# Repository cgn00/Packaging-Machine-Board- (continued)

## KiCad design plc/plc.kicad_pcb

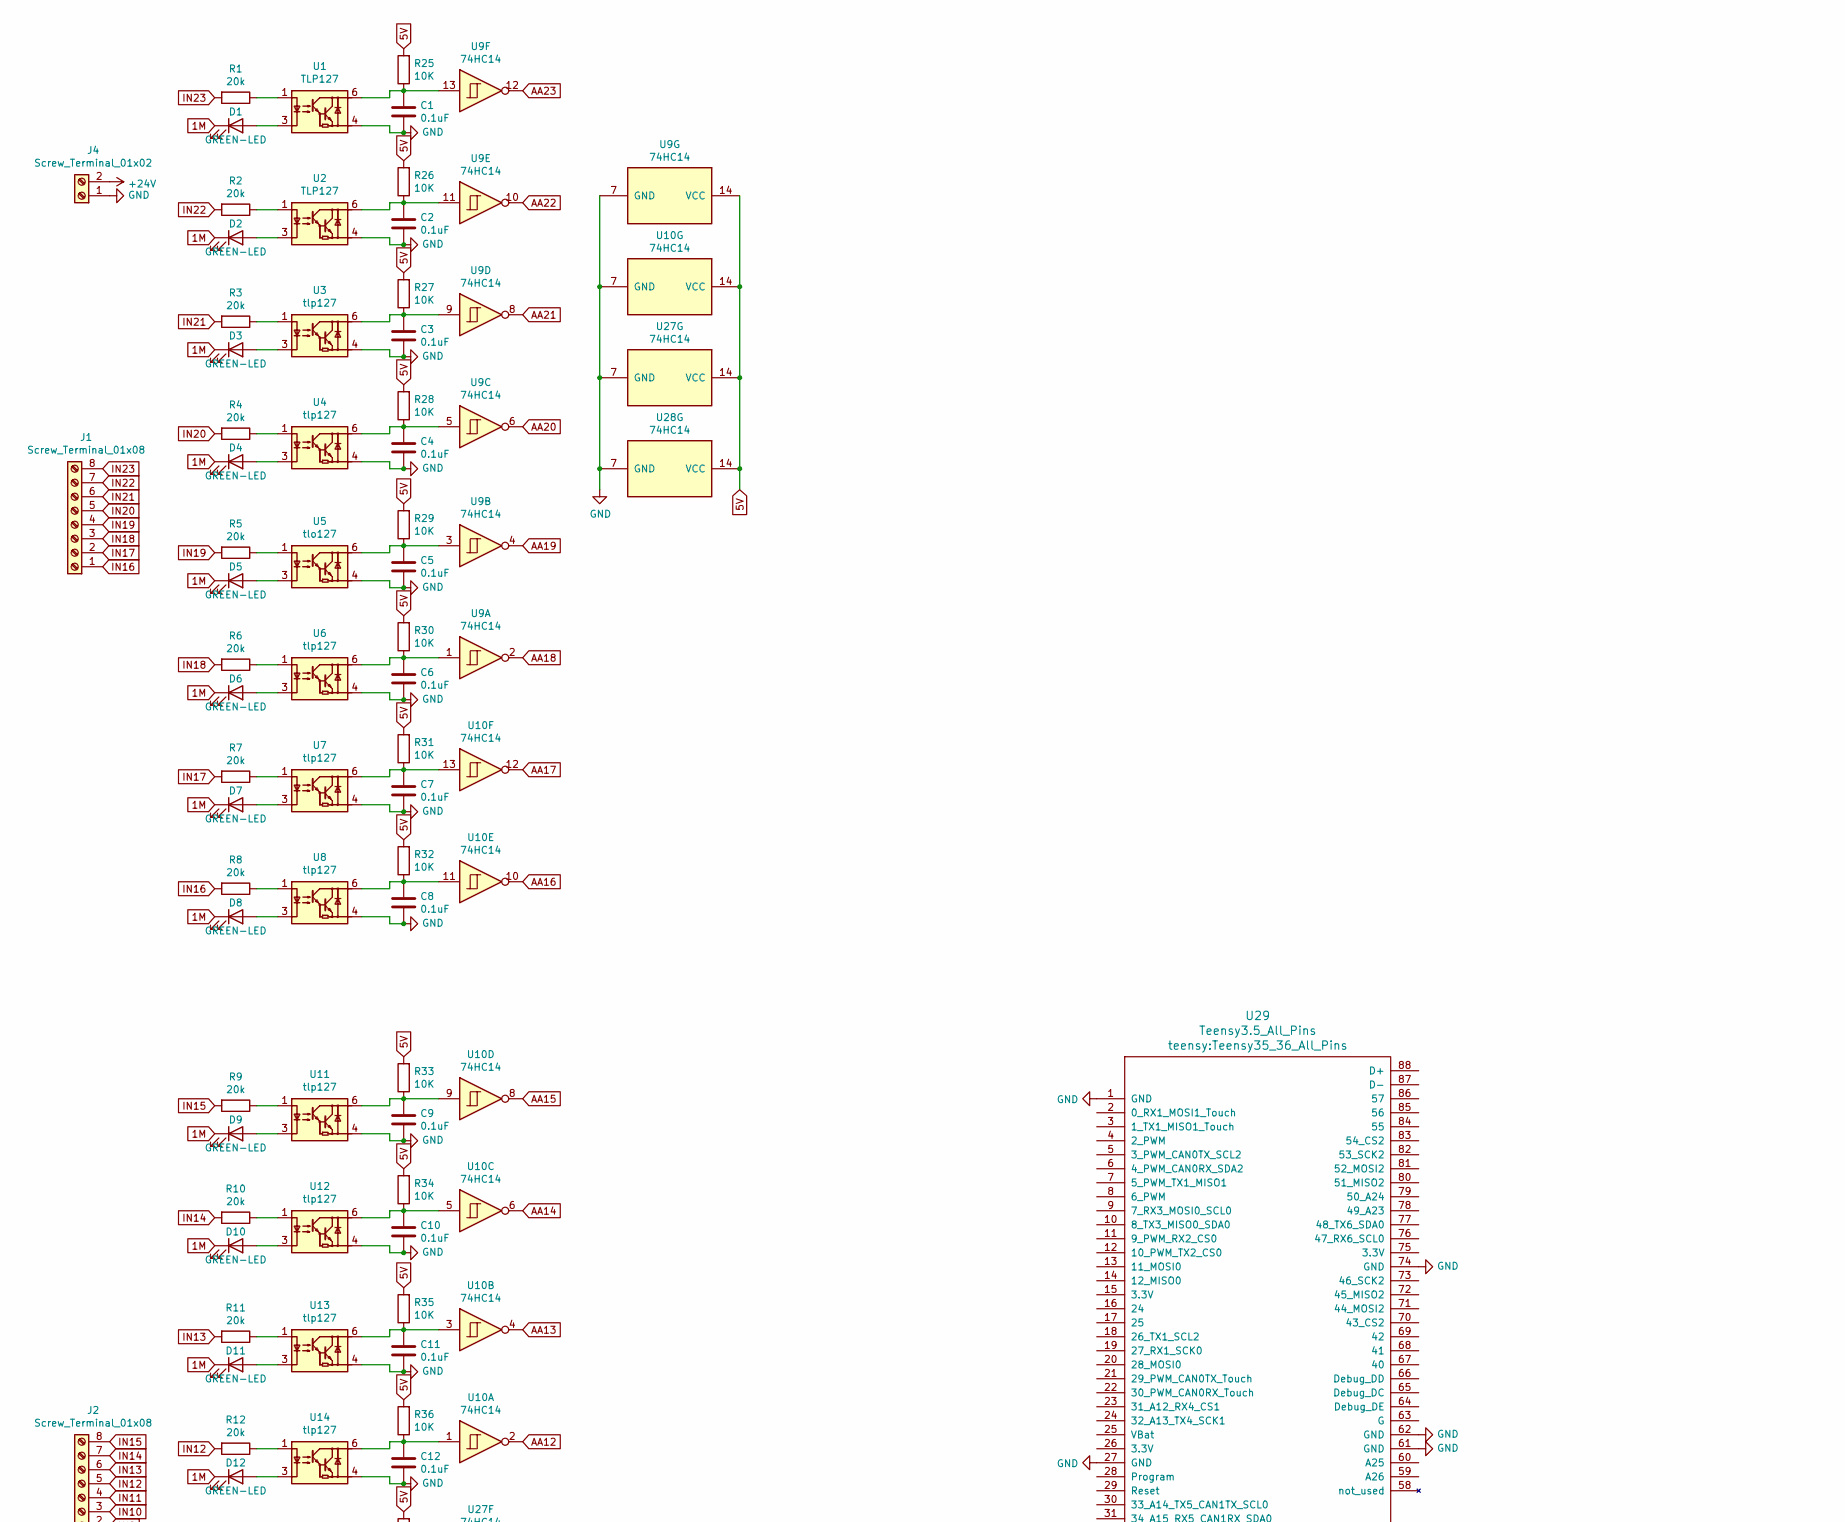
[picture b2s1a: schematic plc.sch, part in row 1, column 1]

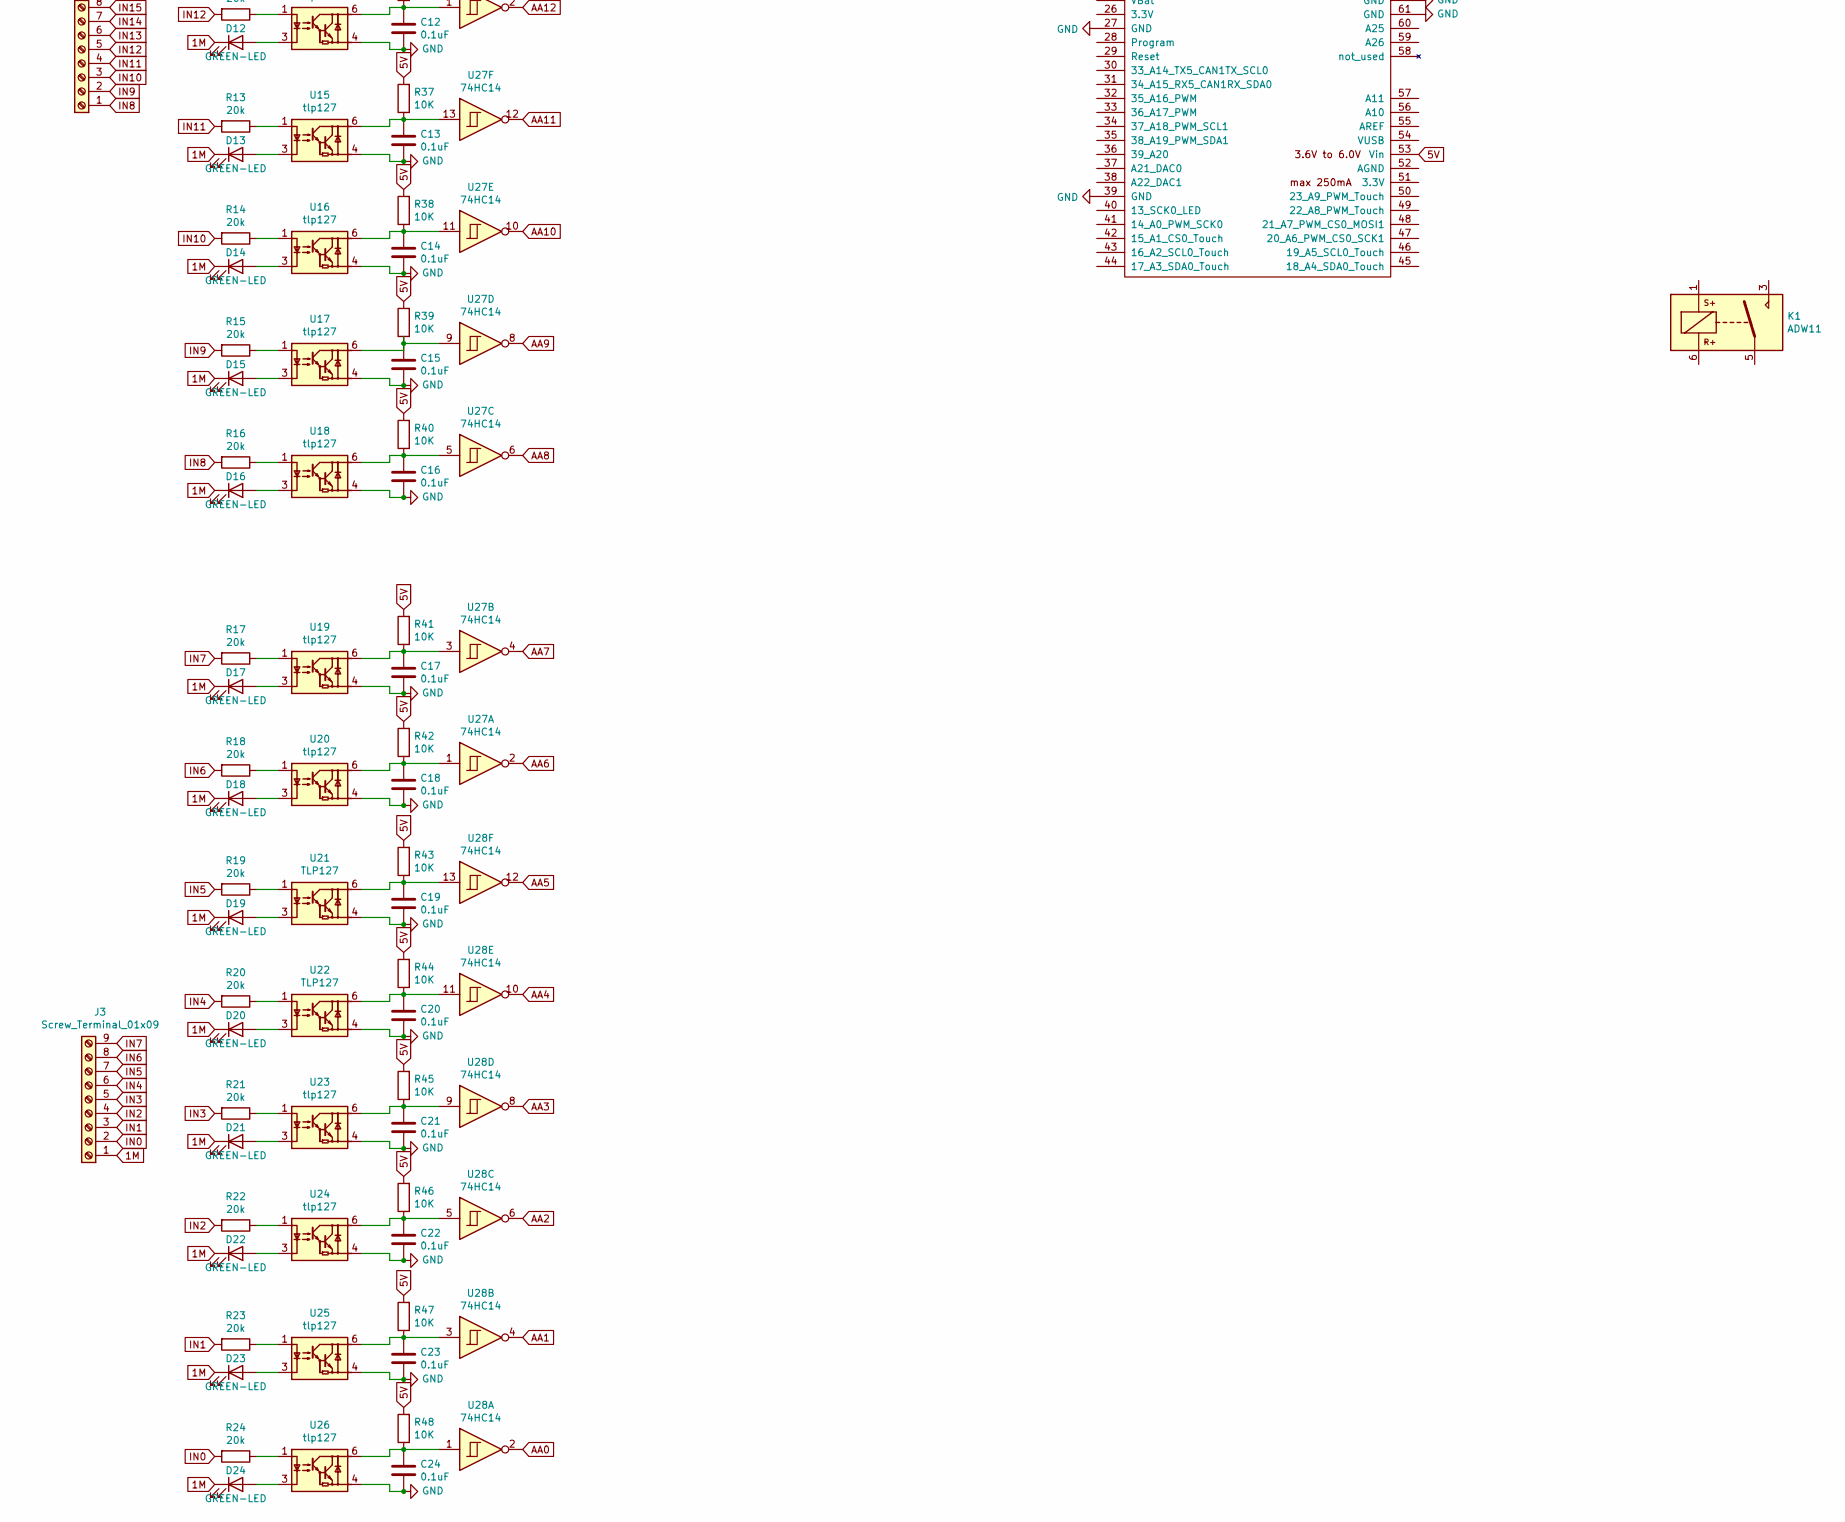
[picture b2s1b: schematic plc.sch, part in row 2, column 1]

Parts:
C1, C2, C3, C4, C5, C6, C7, C8, C9, C10, C11, C12, C13, C14, C15, C16, C17, C18, C19, C20, C21, C22, C23, C24: 0.1uF; C_1206_3216Metric
D1, D2, D3, D4, D5, D6, D7, D8, D9, D10, D11, D12, D13, D14, D15, D16, D17, D18, D19, D20, D21, D22, D23, D24: GREEN-LED; LED_1206_3216Metric_Castellated
J1, J2: Screw_Terminal_01x08; Altech_AK300_1x08_P5.00mm_45-Degree
J3: Screw_Terminal_01x09; Altech_AK300_1x09_P5.00mm_45-Degree
J4: Screw_Terminal_01x02; Altech_AK300_1x02_P5.00mm_45-Degree
K1: ADW11; Relay_1P1T_NO_10x24x18.8mm_Panasonic_ADW11xxxxW_THT
R1, R2, R3, R4, R5, R6, R7, R8, R9, R10, R11, R12, R13, R14, R15, R16, R17, R18, R19, R20, R21, R22, R23, R24: 20k; R_1206_3216Metric_Pad1.30x1.75mm_HandSolder
R25, R26, R27, R28, R29, R30, R31, R32, R33, R34, R35, R36, R37, R38, R39, R40, R41, R42, R43, R44, R45, R46, R47, R48: 10K; R_0603_1608Metric
U1, U2, U21, U22: TLP127; MFSOP6-4_4.4x3.6mm_P1.27mm
U3, U4, U6, U7, U8, U11, U12, U13, U14, U15, U16, U17, U18, U19, U20, U23, U24, U25, U26: tlp127; MFSOP6-4_4.4x3.6mm_P1.27mm
U5: tlo127; MFSOP6-4_4.4x3.6mm_P1.27mm
U9, U10, U27, U28: 74HC14; SOIC-14_3.9x8.7mm_P1.27mm
U29: Teensy3.5_All_Pins; Teensy35_36_All_Pins

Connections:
1M: D1.1 (K), D2.1 (K), D3.1 (K), D4.1 (K), D5.1 (K), D6.1 (K), D7.1 (K), D8.1 (K), D9.1 (K), D10.1 (K), D11.1 (K), D12.1 (K), D13.1 (K), D14.1 (K), D15.1 (K), D16.1 (K), D17.1 (K), D18.1 (K), D19.1 (K), D20.1 (K), D21.1 (K), D22.1 (K), D23.1 (K), D24.1 (K), J3.1
5V: R25.2, R26.2, R27.2, R28.2, R29.2, R30.2, R31.2, R32.2, R33.2, R34.2, R35.2, R36.2, R37.2, R38.2, R39.2, R40.2, R41.2, R42.2, R43.2, R44.2, R45.2, R46.2, R47.2, R48.2, U9.14 (VCC), U10.14 (VCC), U27.14 (VCC), U28.14 (VCC), U29.53 (Vin)
+24V: J4.2
AA0: U28.2
AA1: U28.4
AA2: U28.6
AA3: U28.8
AA4: U28.10
AA5: U28.12
AA6: U27.2
AA7: U27.4
AA8: U27.6
AA9: U27.8
AA10: U27.10
AA11: U27.12
AA12: U10.2
AA13: U10.4
AA14: U10.6
AA15: U10.8
AA16: U10.10
AA17: U10.12
AA18: U9.2
AA19: U9.4
AA20: U9.6
AA21: U9.8
AA22: U9.10
AA23: U9.12
GND: C1.2, C2.2, C3.2, C4.2, C5.2, C6.2, C7.2, C8.2, C9.2, C10.2, C11.2, C12.2, C13.2, C14.2, C15.2, C16.2, C17.2, C18.2, C19.2, C20.2, C21.2, C22.2, C23.2, C24.2, J4.1, U1.4, U2.4, U3.4, U4.4, U5.4, U6.4, U7.4, U8.4, U9.7 (GND), U10.7 (GND), U11.4, U12.4, U13.4, U14.4, U15.4, U16.4, U17.4, U18.4, U19.4, U20.4, U21.4, U22.4, U23.4, U24.4, U25.4, U26.4, U27.7 (GND), U28.7 (GND), U29.1 (GND), U29.27 (GND), U29.39 (GND), U29.61 (GND), U29.62 (GND), U29.74 (GND)
IN0: J3.2, R24.2
IN1: J3.3, R23.2
IN2: J3.4, R22.2
IN3: J3.5, R21.2
IN4: J3.6, R20.2
IN5: J3.7, R19.2
IN6: J3.8, R18.2
IN7: J3.9, R17.2
IN8: J2.1, R16.2
IN9: J2.2, R15.2
IN10: J2.3, R14.2
IN11: J2.4, R13.2
IN12: J2.5, R12.2
IN13: J2.6, R11.2
IN14: J2.7, R10.2
IN15: J2.8, R9.2
IN16: J1.1, R8.2
IN17: J1.2, R7.2
IN18: J1.3, R6.2
IN19: J1.4, R5.2
IN20: J1.5, R4.2
IN21: J1.6, R3.2
IN22: J1.7, R2.2
IN23: J1.8, R1.2
unnamed: C1.1, R25.1, U1.6, U9.13
unnamed: C2.1, R26.1, U2.6, U9.11
unnamed: C3.1, R27.1, U3.6, U9.9
unnamed: C4.1, R28.1, U4.6, U9.5
unnamed: C5.1, R29.1, U5.6, U9.3
unnamed: C6.1, R30.1, U6.6, U9.1
unnamed: C7.1, R31.1, U7.6, U10.13
unnamed: C8.1, R32.1, U8.6, U10.11
unnamed: C9.1, R33.1, U10.9, U11.6
unnamed: C10.1, R34.1, U10.5, U12.6
unnamed: C11.1, R35.1, U10.3, U13.6
unnamed: C12.1, R36.1, U10.1, U14.6
unnamed: C13.1, R37.1, U15.6, U27.13
unnamed: C14.1, R38.1, U16.6, U27.11
unnamed: C15.1, R39.1, U17.6, U27.9
unnamed: C16.1, R40.1, U18.6, U27.5
unnamed: C17.1, R41.1, U19.6, U27.3
unnamed: C18.1, R42.1, U20.6, U27.1
unnamed: C19.1, R43.1, U21.6, U28.13
unnamed: C20.1, R44.1, U22.6, U28.11
unnamed: C21.1, R45.1, U23.6, U28.9
unnamed: C22.1, R46.1, U24.6, U28.5
unnamed: C23.1, R47.1, U25.6, U28.3
unnamed: C24.1, R48.1, U26.6, U28.1
unnamed: D1.2 (A), U1.3
unnamed: D2.2 (A), U2.3
unnamed: D3.2 (A), U3.3
unnamed: D4.2 (A), U4.3
unnamed: D5.2 (A), U5.3
unnamed: D6.2 (A), U6.3
unnamed: D7.2 (A), U7.3
unnamed: D8.2 (A), U8.3
unnamed: D9.2 (A), U11.3
unnamed: D10.2 (A), U12.3
unnamed: D11.2 (A), U13.3
unnamed: D12.2 (A), U14.3
unnamed: D13.2 (A), U15.3
unnamed: D14.2 (A), U16.3
unnamed: D15.2 (A), U17.3
unnamed: D16.2 (A), U18.3
unnamed: D17.2 (A), U19.3
unnamed: D18.2 (A), U20.3
unnamed: D19.2 (A), U21.3
unnamed: D20.2 (A), U22.3
unnamed: D21.2 (A), U23.3
unnamed: D22.2 (A), U24.3
unnamed: D23.2 (A), U25.3
unnamed: D24.2 (A), U26.3
unnamed: R1.1, U1.1
unnamed: R2.1, U2.1
unnamed: R3.1, U3.1
unnamed: R4.1, U4.1
unnamed: R5.1, U5.1
unnamed: R6.1, U6.1
unnamed: R7.1, U7.1
unnamed: R8.1, U8.1
unnamed: R9.1, U11.1
unnamed: R10.1, U12.1
unnamed: R11.1, U13.1
unnamed: R12.1, U14.1
unnamed: R13.1, U15.1
unnamed: R14.1, U16.1
unnamed: R15.1, U17.1
unnamed: R16.1, U18.1
unnamed: R17.1, U19.1
unnamed: R18.1, U20.1
unnamed: R19.1, U21.1
unnamed: R20.1, U22.1
unnamed: R21.1, U23.1
unnamed: R22.1, U24.1
unnamed: R23.1, U25.1
unnamed: R24.1, U26.1

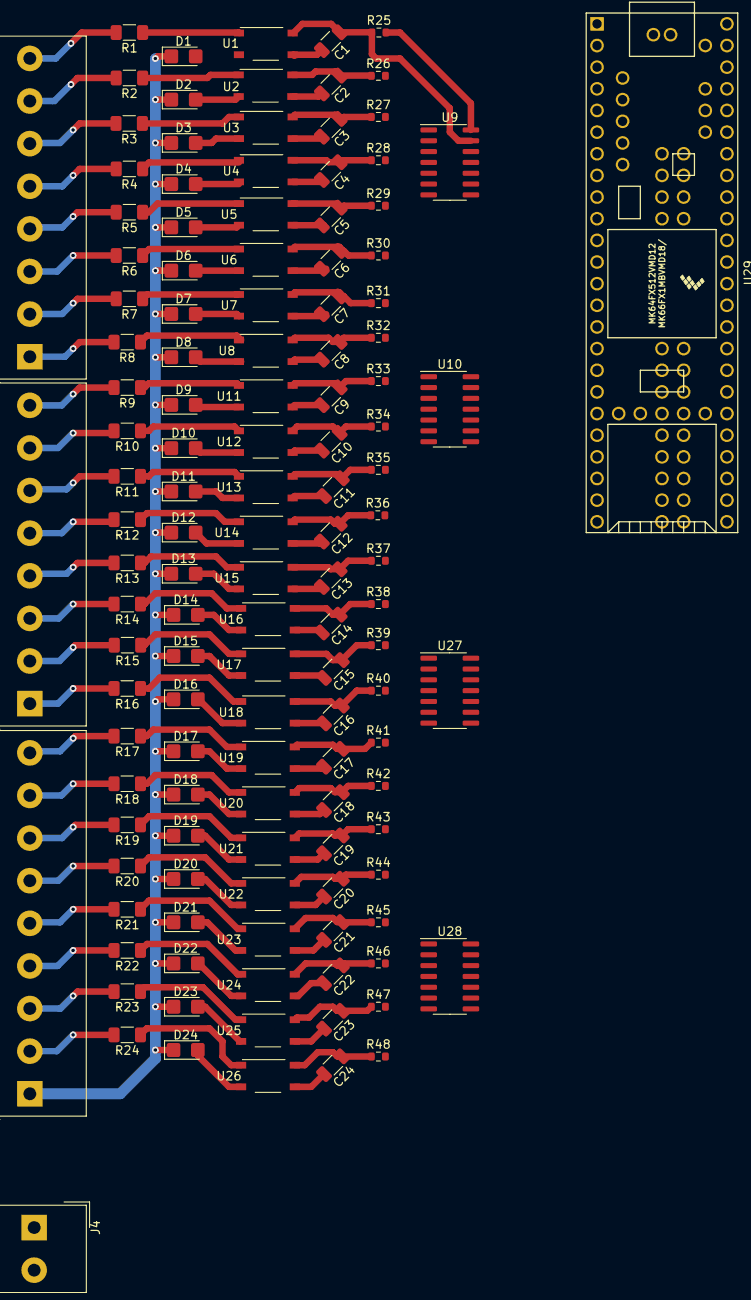
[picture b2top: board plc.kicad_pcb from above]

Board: 2 copper layers, 129 parts (0 on the bottom side), 99 nets.

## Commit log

2022-09-26 Initial commit.
2022-09-26 Testing git.
    This new version has a wire unconnected in the schematic.
2022-10-16 Added the PWM output with IGBT, the ethernet port.
2022-10-24 Version 1 lista con gerbers
2022-11-12 Added a 3.3V and 5V pins Also commented the regulator used, and how to wire VGE and VGE1
2022-11-12 Added the RS232 and RS485 to the BOM
